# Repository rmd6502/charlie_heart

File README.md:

Charlie Heart
=============

https://dl.dropboxusercontent.com/u/10205003/VIDEO0005.mp4
Charlieplexed Heart for Mother's day, etc.  The files are for EAGLE cad, will gladly accept pull requests with Kicad files.

David Reeves made a set of step-by-step instructional photos at https://www.flickr.com/photos/dcreeves2000/sets/72157640155673266/

Annie Hsu made me an instructional video at https://www.dropbox.com/s/pq46bvkq2qu05k4/LED%20Heart-SD%20for%20Apple%20Devices.m4v

Parts Manifest
==============

1.  Heart-shaped circuit board
1.  5 x 3Ω resistors, marking "3R0"
1.  1 x 1kΩ resistor, marking "102"
1.  1 x .1µf capacitor, tan
1.  1 x mosfet transistor
1.  1 x pushbutton switch
1.  1 x preprogrammed ATTiny85 processor
1.  20 x red LEDs
1.  1 x battery clip
1.  1 x CR2032 battery

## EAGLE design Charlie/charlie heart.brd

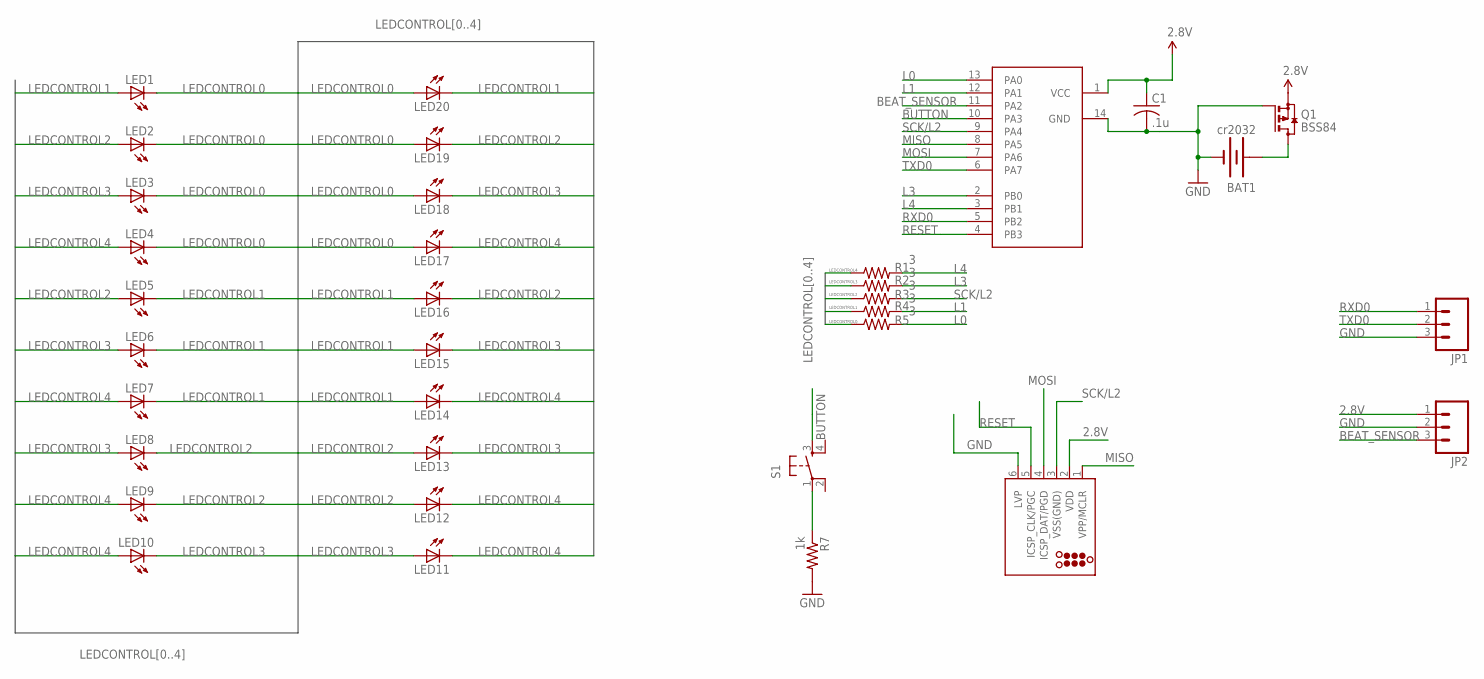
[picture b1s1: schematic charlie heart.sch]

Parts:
BAT1: cr2032; BATTCON_20MM
C1: .1u; C1206
J1: TC2030-MCP-NL
JP1, JP2: M031X03_NO_SILK; 1X03_NO_SILK
LED1, LED2, LED3, LED4, LED5, LED6, LED7, LED8, LED9, LED10, LED11, LED12, LED13, LED14, LED15, LED16, LED17, LED18, LED19, LED20: LEDCHIP-LED0805; CHIP-LED0805
Q1: BSS84; SOT23
R1, R2, R3, R4, R5: 3; R0805
R7: 1k; R0805
S1: TAC_SWITCHSMD; TACTILE_SWITCH_SMD
U1: ATTINY841; SOIC127P600X175-14N

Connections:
2.8V: C1.1, J1.2 (VDD), JP2.1, Q1.2 (S), U1.1 (VCC)
BEAT_SENSOR: JP2.3, U1.11 (PA2)
BUTTON: S1.3, U1.10 (PA3)
GND: BAT1.2 (-), C1.2, J1.6 (LVP), JP1.3, JP2.2, Q1.1 (G), R7.2, U1.14 (GND)
L0: R5.2, U1.13 (PA0)
L1: R4.2, U1.12 (PA1)
L3: R2.2, U1.2 (PB0)
L4: R1.2, U1.3 (PB1)
LEDCONTROL0: LED1.C, LED2.C, LED3.C, LED4.C, LED17.A, LED18.A, LED19.A, LED20.A, R5.1
LEDCONTROL1: LED1.A, LED5.C, LED6.C, LED7.C, LED14.A, LED15.A, LED16.A, LED20.C, R4.1
LEDCONTROL2: LED2.A, LED5.A, LED8.C, LED9.C, LED12.A, LED13.A, LED16.C, LED19.C, R3.1
LEDCONTROL3: LED3.A, LED6.A, LED8.A, LED10.C, LED11.A, LED13.C, LED15.C, LED18.C, R2.1
LEDCONTROL4: LED4.A, LED7.A, LED9.A, LED10.A, LED11.C, LED12.C, LED14.C, LED17.C, R1.1
MISO: J1.1 (VPP/MCLR), U1.8 (PA5)
MOSI: J1.4 (ICSP_DAT/PGD), U1.7 (PA6)
unnamed: BAT1.1 (+), Q1.3 (D)
unnamed: R7.1, S1.1
RESET: J1.5 (ICSP_CLK/PGC), U1.4 (PB3)
RXD0: JP1.1, U1.5 (PB2)
SCK/L2: J1.3 (VSS(GND)), R3.2, U1.9 (PA4)
TXD0: JP1.2, U1.6 (PA7)

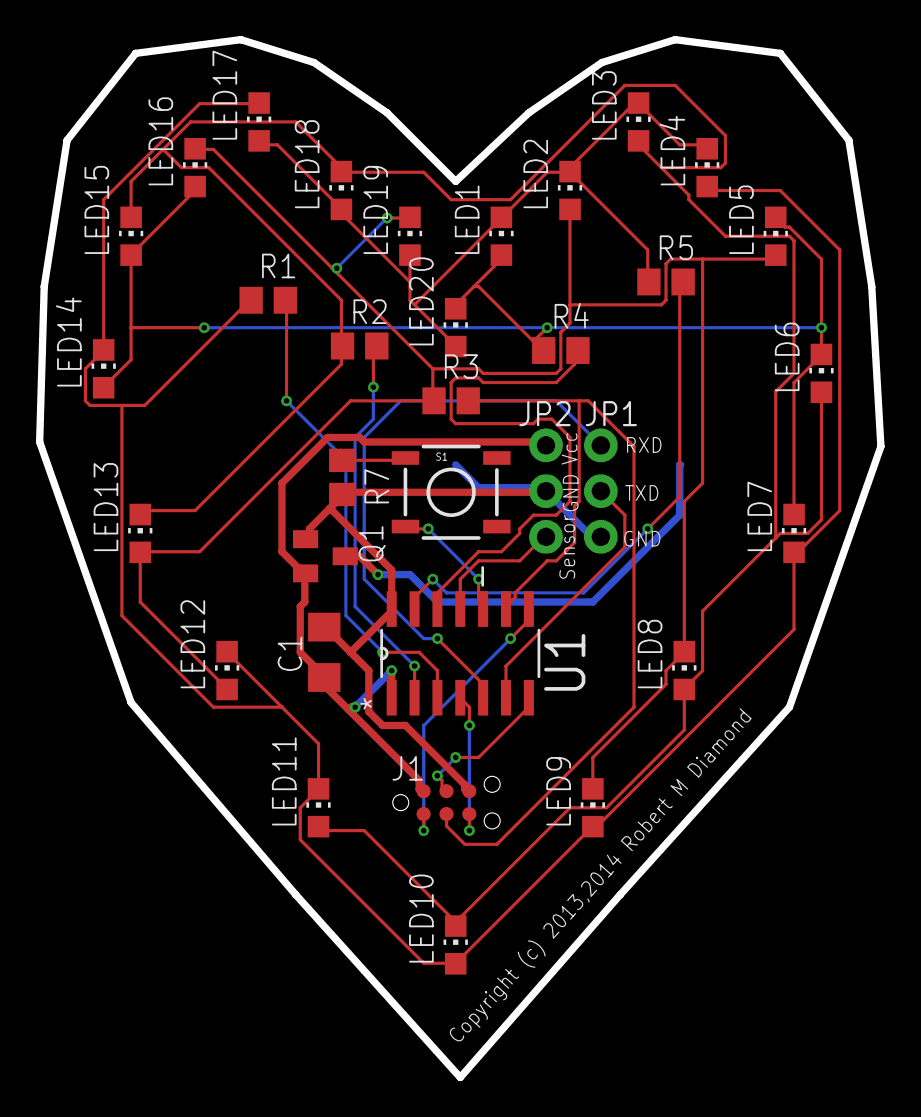
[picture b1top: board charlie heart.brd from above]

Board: 2 copper layers, 46.7 x 57.7 mm, 34 parts (1 on the bottom side), 21 nets.

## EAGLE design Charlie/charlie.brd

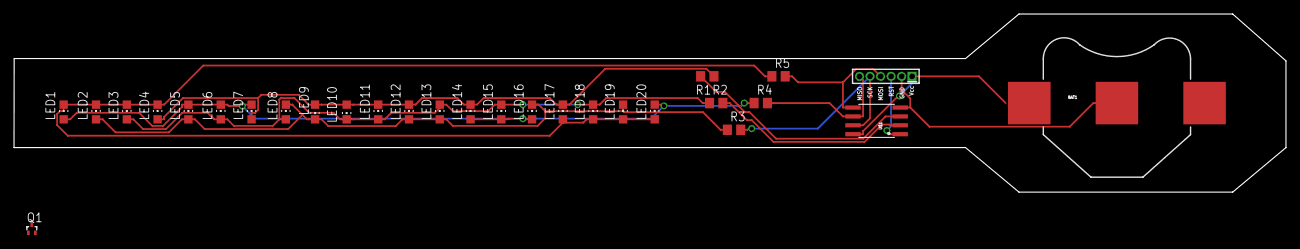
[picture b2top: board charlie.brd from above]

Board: 2 copper layers, 181.4 x 25.4 mm, 29 parts (0 on the bottom side), 13 nets.

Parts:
BAT1: cr2032; BATTCON_20MM
LED1, LED2, LED3, LED4, LED5, LED6, LED7, LED8, LED9, LED10, LED11, LED12, LED13, LED14, LED15, LED16, LED17, LED18, LED19, LED20: CHIP-LED0805
Q1: BSA223SP; SC75_INFINEON
R1, R2, R3, R4, R5: 3; R0805
U$1: ATTINY45; SO08-EIAJ
U$3: AVR_MINI_PROGSMD; AVR_MINI_PROG

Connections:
2.8V: Q1.3, U$1.8, U$3.1
GND: BAT1.2, Q1.1, U$1.4, U$3.2
LEDCONTROL0: LED1.C, LED2.C, LED3.C, LED4.C, LED17.A, LED18.A, LED19.A, LED20.A, R5.1
LEDCONTROL1: LED1.A, LED5.C, LED6.C, LED7.C, LED14.A, LED15.A, LED16.A, LED20.C, R4.1
LEDCONTROL2: LED2.A, LED5.A, LED8.C, LED9.C, LED12.A, LED13.A, LED16.C, LED19.C, R3.1
LEDCONTROL3: LED3.A, LED6.A, LED8.A, LED10.C, LED11.A, LED13.C, LED15.C, LED18.C, R2.1
LEDCONTROL4: LED4.A, LED7.A, LED9.A, LED10.A, LED11.C, LED12.C, LED14.C, LED17.C, R1.1
unnamed: R5.2, U$1.5, U$3.4
unnamed: R4.2, U$1.6, U$3.6
unnamed: R3.2, U$1.7, U$3.5
unnamed: R2.2, U$1.2
unnamed: R1.2, U$1.3
RESET: U$1.1, U$3.3

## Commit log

2012-08-20 initial import
2012-08-20 make it compile, but I'm sure it doesn't work yet
2013-05-11 finally working as it should, now for tweaks and stuff
2013-05-11 add video of heart in action
2013-05-11 add video to markdown
2013-05-11 complete circle
2013-05-12 use timer0 and PRR to conserve battery
2013-05-12 add 3d printed frame files
2013-05-12 update video link
2013-05-12 remove local video
2013-08-02 add program target to makefile
2013-08-03 add comment
2013-08-03 add proper board file, and add mosfet for reverse battery safety
2013-08-03 add mode switch
2013-08-03 add copyright and email address QR
2013-08-03 flip qr code so it's right
2013-08-04 remove pullup resistor
2013-08-10 button, pll clock
2013-08-27 add button driver
2013-08-27 update board font, button pin
2013-08-29 also add button support
2013-08-29 multiple states, power down
2013-08-29 fix typos
2013-08-31 add pulse
2013-09-08 not yet functional
2013-09-08 fix charlie init
2013-09-08 I think that will work
2013-09-08 button support
2013-09-14 pulse measure mode
2013-09-21 back to the default patterns
2013-09-21 fix sleep mode
2013-09-21 also clear flash before sleep
2013-09-21 pulse mode timing
2013-09-22 further enhancements. enable adc when using it
2013-10-09 Fixed scanner mode
2013-10-10 adc tests
2013-10-12 add alternate mode
2013-10-12 uncrustify
2013-10-15 check
2013-10-15 add import
2014-01-25 pulse_adc
2014-01-26 more adc
2014-01-26 temp
2014-01-26 update frame
2014-01-26 new readme
2014-01-26 new board with tiny841
2014-01-26 new board
2014-01-26 constrain reading to avoid hangs
2014-01-26 range
2014-01-26 add jumpers for serial and beat sensor
2014-01-28 update PDFs
2014-01-28 add solder paste template
2014-01-29 update template
2014-01-29 update svg
2014-02-10 update program lines
2014-02-22 pins
2014-02-22 start moving to pins
2014-02-22 pullups
2014-02-23 compiles but needs work in pins
2014-02-23 pullup
2014-03-03 fix pins
2014-03-03 fix timing
2014-03-04 fix1
2014-03-04 pulse mode
2014-03-04 timing
2014-09-08 update links
2014-09-08 update link again
2014-09-08 remove movie link
2014-09-08 add back video
2014-09-08 add manifest

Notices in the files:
Charlie/charlie heart.brd:
Copyright (c) 2013,2014 Robert M Diamond
parts and their libraries:
tag-connect: ©2009 ROFA.cz - modified and updated by Robert Darlington ‹rdarlington@gmail.com›
SparkFun-Aesthetics: Licensing: CC v3.0 Share-Alike You are welcome to use this library for commercial purposes.
